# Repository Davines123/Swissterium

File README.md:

# MYSTERIUM
**TKL keyboard that can be entirely assembled using only through hole components, including usb type c**

**[BOM, Build Guide, and Flashing Information](./doc)**

**Kits available at [cftkb.com](https://www.cftkb.com)**

**[Optional High Profile Lasercut Acrylic Case](./case)**

Currently WIP

V1 - Initial Commit

V2 - Cleaning up, fix isolated GND plane, switched left shift to 2.25u, added 3800 stepped capslock

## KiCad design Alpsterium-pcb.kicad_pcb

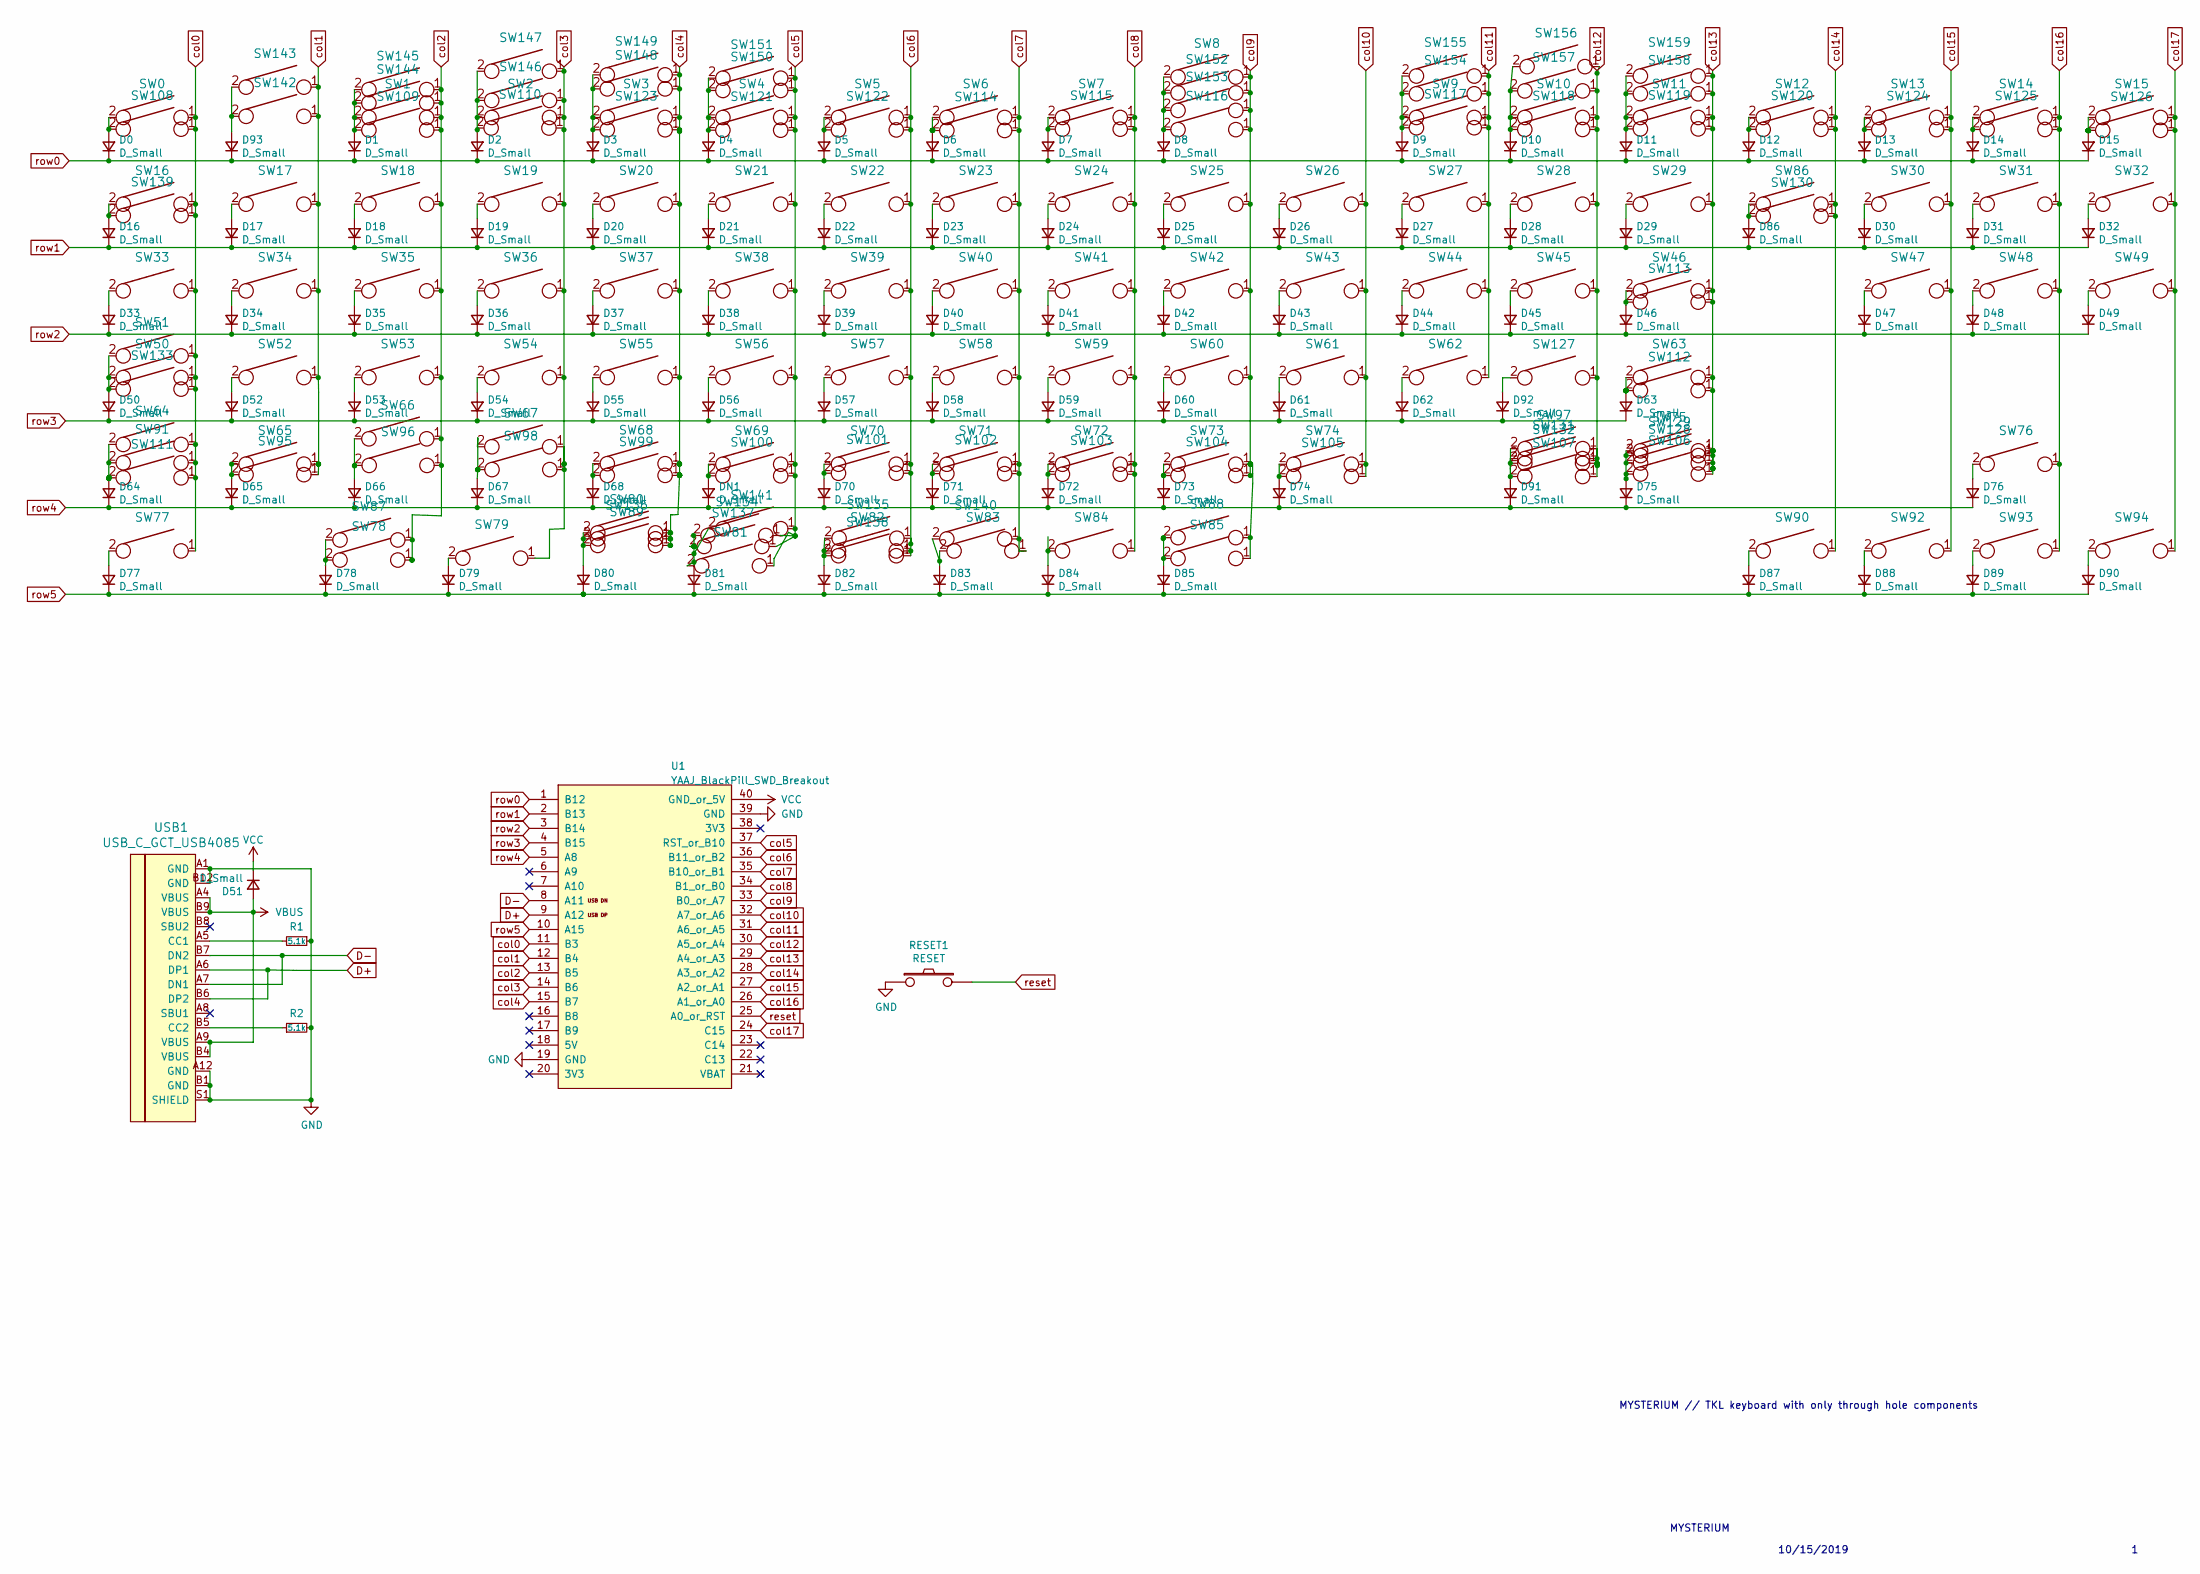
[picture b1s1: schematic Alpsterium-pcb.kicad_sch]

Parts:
D0, D1, D2, D3, D4, D5, D6, D7, D8, D9, D10, D11, D12, D13, D14, D15, D16, D17, D18, D19, D20, D21, D22, D23, D24, D25, D26, D27, D28, D29, D30, D31, D32, D33, D34, D35, D36, D37, D38, D39, D40, D41, D42, D43, D44, D45, D46, D47, D48, D49, D50, D51, D52, D53, D54, D55, D56, D57, D58, D59, D60, D61, D62, D63, D64, D65, D66, D67, D68, D70, D71, D72, D73, D74, D75, D76, D77, D78, D79, D80, D81, D82, D83, D84, D85, D86, D87, D88, D89, D90, D91, D92, D93: D_Small; D_DO-35_SOD27_P5.08mm_Horizontal
DN1: D_Small; D_DO-35_SOD27_P5.08mm_Horizontal
R1, R2: 5.1k; R_Axial_DIN0204_L3.6mm_D1.6mm_P7.62mm_Horizontal
RESET1: RESET; SW_PUSH_6mm
SW0, SW1, SW2, SW3, SW4, SW5, SW6, SW7, SW8, SW9, SW10, SW11, SW12, SW13, SW14, SW15, SW16, SW17, SW18, SW19, SW20, SW21, SW22, SW23, SW24, SW25, SW26, SW27, SW28, SW29, SW30, SW31, SW32, SW34, SW35, SW36, SW37, SW38, SW39, SW40, SW41, SW42, SW43, SW44, SW45, SW47, SW48, SW49, SW52, SW53, SW54, SW55, SW56, SW57, SW58, SW59, SW60, SW61, SW62, SW63, SW65, SW66, SW67, SW68, SW69, SW70, SW71, SW72, SW73, SW74, SW76, SW78, SW79, SW84, SW85, SW86, SW92, SW93, SW94, SW95, SW96, SW97, SW98, SW99, SW100, SW101, SW102, SW103, SW104, SW105, SW107, SW129, SW132, SW143, SW145, SW147, SW149, SW151, SW153, SW154, SW157, SW158: KEYSW; MX-1U-NoLED
SW33, SW77, SW80, SW81, SW82, SW83, SW87, SW88, SW90, SW113, SW133, SW135, SW140: KEYSW; MX-1.5U-NoLED
SW46: KEYSW; MX-ISO-ReversedStabilizers
SW50, SW128, SW131: KEYSW; MX-1.75U-NoLED
SW51, SW91, SW127: KEYSW; MX-1.25U-NoLED
SW64, SW75, SW130, SW136, SW137, SW138: KEYSW; MX-2U-NoLED
SW89: KEYSW; MX-7U-ReversedStabilizers-NoLED
SW106: KEYSW; MX-2.75U-ReversedStabilizers-NoLED
SW108, SW109, SW110, SW114, SW115, SW116, SW117, SW118, SW119, SW120, SW121, SW122, SW123, SW124, SW125, SW126, SW139, SW142, SW144, SW146, SW148, SW150, SW152, SW155, SW156, SW159: KEYSW; ALPS-1U
SW111, SW112: KEYSW; MX-2.25U-ReversedStabilizers-NoLED
SW134: KEYSW; MX-2.5U-ReversedStabilizers-NoLED
SW141: KEYSW; MX-6.5U-FLIPPED-NoStabilizers
U1: YAAJ_BlackPill_SWD_Breakout; DIP-40_W15.24mm_Socket
USB1: USB_C_GCT_USB4085

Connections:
D+: U1.9 (A12), USB1.A6 (DP1), USB1.B6 (DP2)
D-: U1.8 (A11), USB1.A7 (DN1), USB1.B7 (DN2)
GND: R1.1, R2.2, RESET1.1, U1.19 (GND), U1.39 (GND), USB1.A1 (GND), USB1.A12 (GND), USB1.B1 (GND), USB1.B12 (GND), USB1.S1 (SHIELD)
unnamed: D0.2 (A), SW0.2, SW108.2
unnamed: D1.2 (A), SW1.2, SW109.2, SW144.2, SW145.2
unnamed: D2.2 (A), SW2.2, SW110.2, SW146.2, SW147.2
unnamed: D3.2 (A), SW3.2, SW123.2, SW148.2, SW149.2
unnamed: D4.2 (A), SW4.2, SW121.2, SW150.2, SW151.2
unnamed: D5.2 (A), SW5.2, SW122.2
unnamed: D6.2 (A), SW6.2, SW114.2
unnamed: D7.2 (A), SW7.2, SW115.2
unnamed: D8.2 (A), SW8.2, SW116.2, SW152.2, SW153.2
unnamed: D9.2 (A), SW9.2, SW117.2, SW154.2, SW155.2
unnamed: D10.2 (A), SW10.2, SW118.2, SW156.2, SW157.2
unnamed: D11.2 (A), SW11.2, SW119.2, SW158.2, SW159.2
unnamed: D12.2 (A), SW12.2, SW120.2
unnamed: D13.2 (A), SW13.2, SW124.2
unnamed: D14.2 (A), SW14.2, SW125.2
unnamed: D15.2 (A), SW15.2, SW126.2
unnamed: D16.2 (A), SW16.2, SW139.2
unnamed: D17.2 (A), SW17.2
unnamed: D18.2 (A), SW18.2
unnamed: D19.2 (A), SW19.2
unnamed: D20.2 (A), SW20.2
unnamed: D21.2 (A), SW21.2
unnamed: D22.2 (A), SW22.2
unnamed: D23.2 (A), SW23.2
unnamed: D24.2 (A), SW24.2
unnamed: D25.2 (A), SW25.2
unnamed: D26.2 (A), SW26.2
unnamed: D27.2 (A), SW27.2
unnamed: D28.2 (A), SW28.2
unnamed: D29.2 (A), SW29.2
unnamed: D30.2 (A), SW30.2
unnamed: D31.2 (A), SW31.2
unnamed: D32.2 (A), SW32.2
unnamed: D33.2 (A), SW33.2
unnamed: D34.2 (A), SW34.2
unnamed: D35.2 (A), SW35.2
unnamed: D36.2 (A), SW36.2
unnamed: D37.2 (A), SW37.2
unnamed: D38.2 (A), SW38.2
unnamed: D39.2 (A), SW39.2
unnamed: D40.2 (A), SW40.2
unnamed: D41.2 (A), SW41.2
unnamed: D42.2 (A), SW42.2
unnamed: D43.2 (A), SW43.2
unnamed: D44.2 (A), SW44.2
unnamed: D45.2 (A), SW45.2
unnamed: D46.2 (A), SW46.2, SW113.2
unnamed: D47.2 (A), SW47.2
unnamed: D48.2 (A), SW48.2
unnamed: D49.2 (A), SW49.2
unnamed: D50.2 (A), SW50.2, SW51.2, SW133.2
unnamed: D52.2 (A), SW52.2
unnamed: D53.2 (A), SW53.2
unnamed: D54.2 (A), SW54.2
unnamed: D55.2 (A), SW55.2
unnamed: D56.2 (A), SW56.2
unnamed: D57.2 (A), SW57.2
unnamed: D58.2 (A), SW58.2
unnamed: D59.2 (A), SW59.2
unnamed: D60.2 (A), SW60.2
unnamed: D61.2 (A), SW61.2
unnamed: D62.2 (A), SW62.2
unnamed: D63.2 (A), SW63.2, SW112.2
unnamed: D64.2 (A), SW64.2, SW91.2, SW111.2
unnamed: D65.2 (A), SW65.2, SW95.2
unnamed: D66.2 (A), SW66.2, SW96.2
unnamed: D67.2 (A), SW67.2, SW98.2
unnamed: D68.2 (A), SW68.2, SW99.2
unnamed: D70.2 (A), SW70.2, SW101.2
unnamed: D71.2 (A), SW71.2, SW102.2
unnamed: D72.2 (A), SW72.2, SW103.2
unnamed: D73.2 (A), SW73.2, SW104.2
unnamed: D74.2 (A), SW74.2, SW105.2
unnamed: D75.2 (A), SW75.2, SW106.2, SW128.2, SW129.2
unnamed: D76.2 (A), SW76.2
unnamed: D77.2 (A), SW77.2
unnamed: D78.2 (A), SW78.2, SW87.2
unnamed: D79.2 (A), SW79.2
unnamed: D80.2 (A), SW80.2, SW89.2, SW136.2
unnamed: D81.2 (A), SW81.2, SW134.2, SW137.2, SW141.2
unnamed: D82.2 (A), SW82.2, SW135.2, SW138.2
unnamed: D83.2 (A), SW83.2, SW140.2
unnamed: D84.2 (A), SW84.2
unnamed: D85.2 (A), SW85.2, SW88.2
unnamed: D86.2 (A), SW86.2, SW130.2
unnamed: D87.2 (A), SW90.2
unnamed: D88.2 (A), SW92.2
unnamed: D89.2 (A), SW93.2
unnamed: D90.2 (A), SW94.2
unnamed: D91.2 (A), SW107.2, SW131.2, SW132.2
unnamed: D92.2 (A), SW127.2
unnamed: D93.2 (A), SW142.2, SW143.2
unnamed: DN1.2 (A), SW69.2, SW100.2
unnamed: R1.2, USB1.A5 (CC1)
unnamed: R2.1, USB1.B5 (CC2)
VBUS: D51.2 (A), USB1.A4 (VBUS), USB1.A9 (VBUS), USB1.B4 (VBUS), USB1.B9 (VBUS)
VCC: D51.1 (K), U1.40 (GND_or_5V)
col0: SW0.1, SW16.1, SW33.1, SW50.1, SW51.1, SW64.1, SW77.1, SW91.1, SW108.1, SW111.1, SW133.1, SW139.1, U1.11 (B3)
col1: SW17.1, SW34.1, SW52.1, SW65.1, SW95.1, SW142.1, SW143.1, U1.12 (B4)
col2: SW1.1, SW18.1, SW35.1, SW53.1, SW66.1, SW78.1, SW87.1, SW96.1, SW109.1, SW144.1, SW145.1, U1.13 (B5)
col3: SW2.1, SW19.1, SW36.1, SW54.1, SW67.1, SW79.1, SW98.1, SW110.1, SW146.1, SW147.1, U1.14 (B6)
col4: SW3.1, SW20.1, SW37.1, SW55.1, SW68.1, SW80.1, SW89.1, SW99.1, SW123.1, SW136.1, SW148.1, SW149.1, U1.15 (B7)
col5: SW4.1, SW21.1, SW38.1, SW56.1, SW69.1, SW81.1, SW100.1, SW121.1, SW134.1, SW137.1, SW141.1, SW150.1, SW151.1, U1.37 (RST_or_B10)
col6: SW5.1, SW22.1, SW39.1, SW57.1, SW70.1, SW82.1, SW101.1, SW122.1, SW135.1, SW138.1, U1.36 (B11_or_B2)
col7: SW6.1, SW23.1, SW40.1, SW58.1, SW71.1, SW83.1, SW102.1, SW114.1, SW140.1, U1.35 (B10_or_B1)
col8: SW7.1, SW24.1, SW41.1, SW59.1, SW72.1, SW84.1, SW103.1, SW115.1, U1.34 (B1_or_B0)
col9: SW8.1, SW25.1, SW42.1, SW60.1, SW73.1, SW85.1, SW88.1, SW104.1, SW116.1, SW152.1, SW153.1, U1.33 (B0_or_A7)
col10: SW26.1, SW43.1, SW61.1, SW74.1, SW105.1, U1.32 (A7_or_A6)
col11: SW9.1, SW27.1, SW44.1, SW62.1, SW117.1, SW154.1, SW155.1, U1.31 (A6_or_A5)
col12: SW10.1, SW28.1, SW45.1, SW97.1, SW107.1, SW118.1, SW127.1, SW131.1, SW132.1, SW156.1, SW157.1, U1.30 (A5_or_A4)
col13: SW11.1, SW29.1, SW46.1, SW63.1, SW75.1, SW106.1, SW112.1, SW113.1, SW119.1, SW128.1, SW129.1, SW158.1, SW159.1, U1.29 (A4_or_A3)
col14: SW12.1, SW86.1, SW90.1, SW120.1, SW130.1, U1.28 (A3_or_A2)
col15: SW13.1, SW30.1, SW47.1, SW92.1, SW124.1, U1.27 (A2_or_A1)
col16: SW14.1, SW31.1, SW48.1, SW76.1, SW93.1, SW125.1, U1.26 (A1_or_A0)
col17: SW15.1, SW32.1, SW49.1, SW94.1, SW126.1, U1.24 (C15)
reset: RESET1.2, U1.25 (A0_or_RST)
row0: D0.1 (K), D1.1 (K), D2.1 (K), D3.1 (K), D4.1 (K), D5.1 (K), D6.1 (K), D7.1 (K), D8.1 (K), D9.1 (K), D10.1 (K), D11.1 (K), D12.1 (K), D13.1 (K), D14.1 (K), D15.1 (K), D93.1 (K), U1.1 (B12)
row1: D16.1 (K), D17.1 (K), D18.1 (K), D19.1 (K), D20.1 (K), D21.1 (K), D22.1 (K), D23.1 (K), D24.1 (K), D25.1 (K), D26.1 (K), D27.1 (K), D28.1 (K), D29.1 (K), D30.1 (K), D31.1 (K), D32.1 (K), D86.1 (K), U1.2 (B13)
row2: D33.1 (K), D34.1 (K), D35.1 (K), D36.1 (K), D37.1 (K), D38.1 (K), D39.1 (K), D40.1 (K), D41.1 (K), D42.1 (K), D43.1 (K), D44.1 (K), D45.1 (K), D46.1 (K), D47.1 (K), D48.1 (K), D49.1 (K), U1.3 (B14)
row3: D50.1 (K), D52.1 (K), D53.1 (K), D54.1 (K), D55.1 (K), D56.1 (K), D57.1 (K), D58.1 (K), D59.1 (K), D60.1 (K), D61.1 (K), D62.1 (K), D63.1 (K), D92.1 (K), U1.4 (B15)
row4: D64.1 (K), D65.1 (K), D66.1 (K), D67.1 (K), D68.1 (K), D70.1 (K), D71.1 (K), D72.1 (K), D73.1 (K), D74.1 (K), D75.1 (K), D76.1 (K), D91.1 (K), DN1.1 (K), U1.5 (A8)
row5: D77.1 (K), D78.1 (K), D79.1 (K), D80.1 (K), D81.1 (K), D82.1 (K), D83.1 (K), D84.1 (K), D85.1 (K), D87.1 (K), D88.1 (K), D89.1 (K), D90.1 (K), U1.10 (A15)

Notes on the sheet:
MYSTERIUM // TKL keyboard with only through hole components
10/15/2019
MYSTERIUM

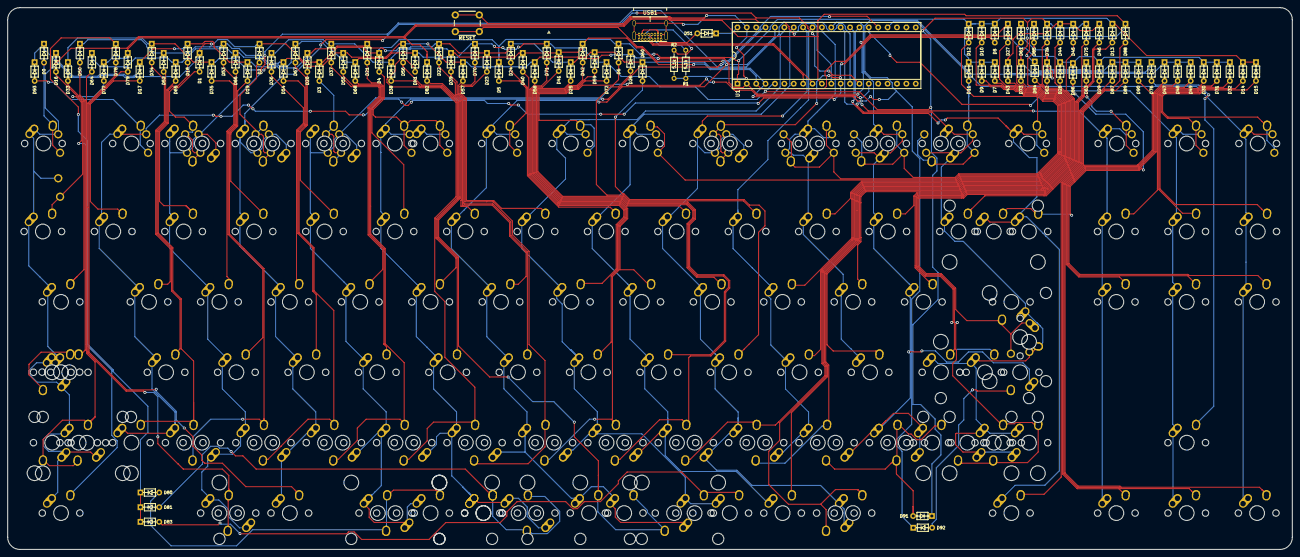
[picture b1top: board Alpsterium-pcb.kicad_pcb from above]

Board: 2 copper layers, 347.7 x 146.6 mm, 259 parts (0 on the bottom side), 125 nets.

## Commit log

2022-01-17 new file: Keebio-Parts.pretty-master/.github/FUNDING.yml new file: Keebio-Parts.pretty-master/3_Pin_Jumper.kicad_mod new file: Keebio-Parts.pretty-master/3dmodels/CUI_SJ-43614-SMT-TR.step new file: K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
2022-01-26 modified: Alpsterium-pcb.dsn modified: Alpsterium-pcb.kicad_pcb modified: Alpsterium-pcb.kicad_sch modified: fp-info-cache
2022-01-26 deleted: ProMicroKiCad-master/LICENSE deleted: ProMicroKiCad-master/README.md deleted: ProMicroKiCad-master/promicro.pretty/ProMicro-EnforcedTop.kicad_mod deleted: ProMicroKiCad-master/promicro.prett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
2022-01-26 modified: Alpsterium-pcb.kicad_sch
